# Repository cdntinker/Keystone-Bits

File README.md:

Some custom Keystone devices...

Once the 3D printable Keystone housings are fully worked out, It'll be cool to have something to use them for.

* **USB-C-C**
  * USB-C pass-thru
* **XT30**
  * XT30 pass-thru
* **I2C Thing**
  * Baseline for I2C based designs
* **ATTiny Thing**
  * Baseline for designs with a built-in MCU
* **RGB Thing**
  * Yay...  Blinkenlights!
* **RGB Thing 2**
  * Double Blinkenlights for Austin

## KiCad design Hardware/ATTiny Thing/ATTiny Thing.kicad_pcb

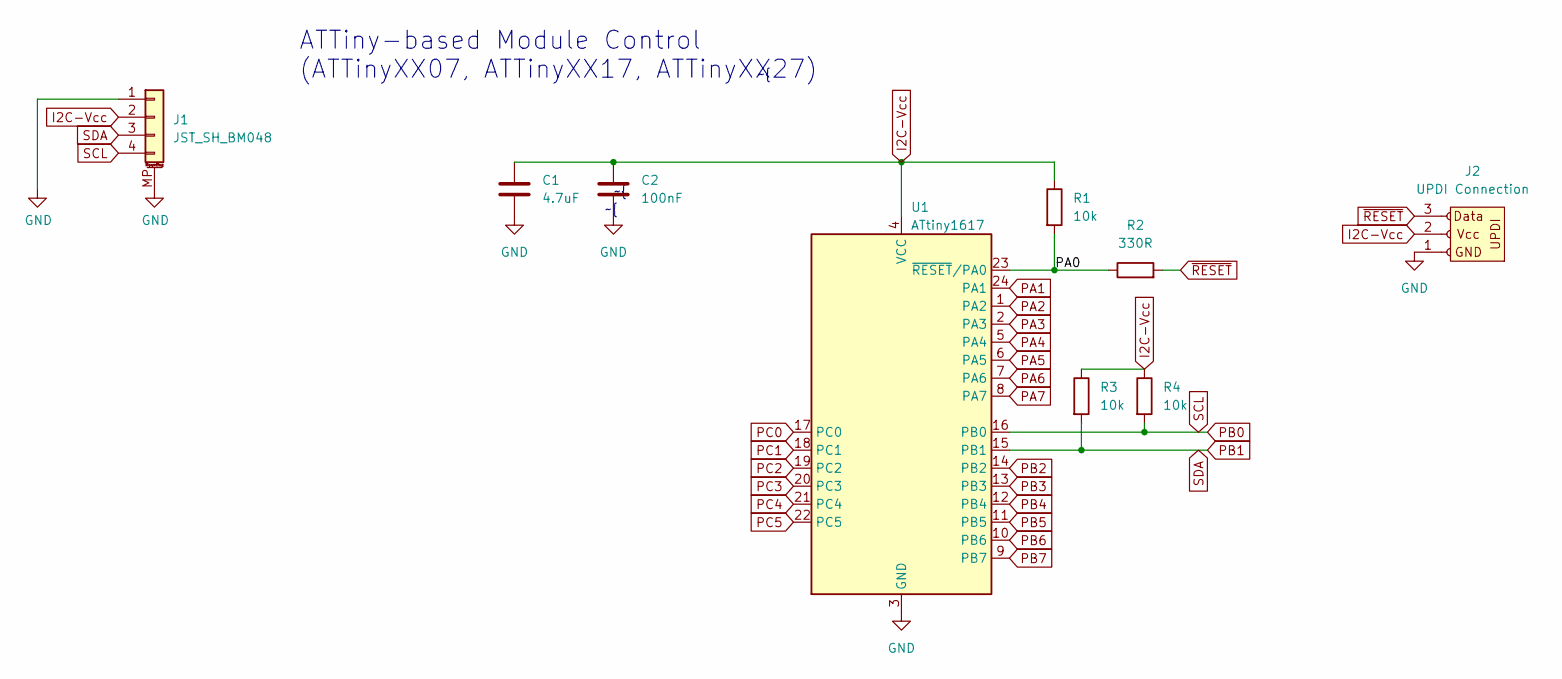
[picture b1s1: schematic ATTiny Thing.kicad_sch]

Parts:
C1: 4.7uF; C_0805_2012Metric; LCSC C107153
C2: 100nF; C_0603_1608Metric; LCSC C14663
J1: JST_SH_BM048; JST_SH_SM04B-SRSS-TB_1x04-1MP_P1.00mm_Horizontal; LCSC C145961
J2: UPDI Connection; UPDI_connection
R1, R3, R4: 10k; R_0603_1608Metric; LCSC C25804
R2: 330R; R_0603_1608Metric; LCSC C23138
U1: ATtiny1617; QFN-24-1EP_4x4mm_P0.5mm_EP2.6x2.6mm; LCSC C1340514

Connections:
/PA0: R1.2, R2.1, U1.23 (~RESET/PA0)
GND: C1.2, C2.2, J1.1, J1.MP (MountPin), J2.1, U1.3 (GND), U1.25 (GND)
I2C-Vcc: C1.1, C2.1, J1.2, J2.2, R1.1, R3.1, R4.1, U1.4 (VCC)
PA1: U1.24 (PA1)
PA2: U1.1 (PA2)
PA3: U1.2 (PA3)
PA4: U1.5 (PA4)
PA5: U1.6 (PA5)
PA6: U1.7 (PA6)
PA7: U1.8 (PA7)
PB0: J1.4, R4.2, U1.16 (PB0)
PB1: J1.3, R3.2, U1.15 (PB1)
PB2: U1.14 (PB2)
PB3: U1.13 (PB3)
PB4: U1.12 (PB4)
PB5: U1.11 (PB5)
PB6: U1.10 (PB6)
PB7: U1.9 (PB7)
PC0: U1.17 (PC0)
PC1: U1.18 (PC1)
PC2: U1.19 (PC2)
PC3: U1.20 (PC3)
PC4: U1.21 (PC4)
PC5: U1.22 (PC5)
~RESET: J2.3, R2.2

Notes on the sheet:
ATTiny-based Module Control (ATTinyXX07, ATTinyXX17, ATTinyXX27)

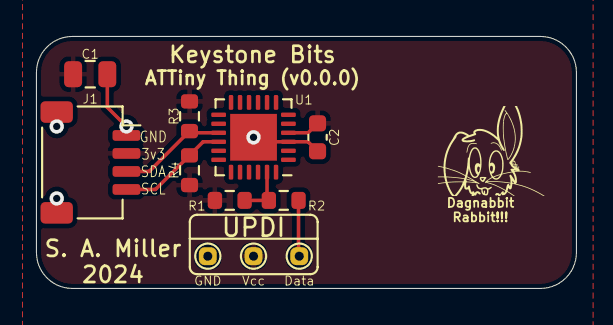
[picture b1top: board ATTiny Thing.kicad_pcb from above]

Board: 2 copper layers, 30.0 x 14.0 mm, 9 parts (0 on the bottom side), 6 nets.

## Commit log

2024-05-03 Added preliminary 3D models
2024-05-03 some pix
2024-05-03 Refined the ATTiny Thing
2024-05-04 moar pix
2024-05-04 Eliminated useless test points... and... NOW WITH RGB!!!
2024-05-06 Found the male XT30 & improved the XT30 board
2024-05-06 SnapEDA responds to issue submissions blindingly fast!
2024-05-06 Pix updates
2024-05-07 Board placement example
